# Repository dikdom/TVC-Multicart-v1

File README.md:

# TVC-Multicart-v1.1
A simple programmodule for the Videoton TVC computer that may contain multiple cartridge images

## English
This package contains the plans of a programmodule for the Videoton TV Compurer. The necessary
parts for building this cart could be obtained easily in 2018 and it costed around 2-3 USD. Cost
of the PCB depends on the manufacturer..

The cart may either contain a hex encoder switch or a 5 element DIP switch. These switches are there
for selecting the usable 16kB or area for the TVC during its startup.
The EEPROM IC has to be programmed, that each cartridge image starts at 16kB boundaries.
The populated EEPROM IC must be pin compatible with the AT29C0x0 (like AM29F0x0 or SST39SF0x0).
Using the HEX encoder one can select up to 16 images, so using an 512kB EEPROM this is not enough (16 images
are just the half of the complete eeprom). That is why there is a pin pad pair for the A18 address line. 
That pin pair must be shorted to access the upper 256kB area (ROM images from 17-32). This jumper is not required
when using the DIP switch, that contains a switch for the A18 line also.
The HEX encoder does the same as the DIP switch: it selects the proper lines on the EEPROM, just it is done by 
rotating the rotary switch.

These schematics were designed using the CADSoft Eagle 8.3.1, free software. The plans (schematics and board layout) 
can also be found, so you may change them at your own will.

You can find the edge connector's library and the cart itself in the eagle-lib directory. The 32k/64k and
the 64k+ machines have different line layout. There is no FAST line and the data lines are gated in the
64k+ machine.

Required parts:
- TVC Multicart v1.1 PCB
- DIP-32 IC socket
- eeprom (eg. SST39SF020)
- 100nF, (min) 16V, 2# ceramic capacitor
- 5+1 resistor network, 10k
- 5 DIP switch, OR
- 16 value hex-encoder

Use it wisely!

Sándor Vass, 2018-09-27

## Magyarul

Ez a csomag egy olyan nyáklap terveit tartalmazza, melyet alkatrésszekkel 
megfelelően ellátva a méltán híres Videoton TV Computerhez egy ún. multicart
cartridge készíthető. A carthoz szükséges alkatrészek 2018-ban kereskedelmi
forgalomban kaphatóak s kb 800Ft-ba kerülnek összesen. A nyáklap legyártásának
költsége gyártófüggő.

A nyáklapon egy forgatható hex enkóder és/vagy egy 5 elemű DIP kapcsolósor 
helyezhető el melyek segítségével lehet kiválasztani, hogy a TVC melyik 16kB -os 
tartományt (bankot) láthassa bekapcsoláskor/resetkor.
Az eeprom ICt úgy kell felprogramozni, hogy 16kB -onként 1-1 cartridge image
kezdődjön, így tudja az adott cartridge image-ét a TVC futtatni.
Az eepromnak lábkompatibilisnek kell lennie az AT29C040 -es ICvel (ilyenek pl.
az AM29F0x0 vagy a SST39SF0x0).
A hex enkóderrel legfeljebb 16 különböző bankot lehet kiválasztani, ez
egy 512kB -os eeprom esetében kevés lenne (pont fele a szükségesnek), ezért 
raktam a lapra egy érintkező párt az A18 lábnak. Ide egy 2x1 -es tüskesor rakható 
(egy jumperrel) vagy egy kapcsoló forrasztható: ezzel lehet kiválasztani, 
hogy az alsó, vagy a fölső 16 bank közül lehessen választani a tekerhető gombbal.
Zárva az érintkező párt az IC A18 -as lába 1-et kap, egyébként 0-át.
A hex-enkóder egy 6 kivezetéses, elforgatható kapcsoló, amely állásától
függően binárisan változtatja a kivezetéseit - 2 GND és 4 kapcsoló láb miatt
van csak 16 lehetséges állapota. Ez a forgatható kapcsoló kiválóan alkalmas az
eeprom A14-A17 lábainak állítására. Ha az eeprom mérete csak 256kB vagy
128kB, akkor nincs szükség a külső kapcsolóra, mert ilyenkor nincs A18 vonal.
A hex-enkóder mellett egy DIP kapcsolósor is beültethető a nyáklapba. Ebben az
esetben sincs szükség a külső kapcsolóra, mivel a DIP kapcsolósor tartalmazza
az A18-as vonal kapcsolóját is.

Ezeket a terveket a CADSoft Eagle 8.3.1, ingyenes verzióval terveztem, a kapcsolási 
rajz (.sch) és a nyákrajzolat (.brd) is mellékelve van, ha változtatásra van szükség.

Megtalálható az eagle-lib könyvtárban alkatrészként a cartrdige élcsatlakozója 
32k/64k és 64k+ gépekhez külön, illetve az egész cartridge, kontúrral, furatokkal
(ahol a gyári cartoknak is a furatuk található), ez szintén 32k/64k és 64k+ gépekhez.
A 64k+ gépeken nincs kivezetve a FAST jel, illetve itt az adatvonalak kapuzva vannak, 
nem közvetlenül a CPU-tól jön a jel.

Szükséges alkatrészek:
- TVC Multicart v1.1 nyáklap
- DIP-32 IC foglalat
- eeprom (pl. SST39SF020)
- 100nF, (min) 16V, 2raszteres kerámia kondenzátor
- 5+1 ellenálláshíd, 10k
- 5 elemű DIP kapcsolósor, vagy
- 16 értékű hex-enkóder

Használd egészséggel!

Vass Sándor, 2018-09-27

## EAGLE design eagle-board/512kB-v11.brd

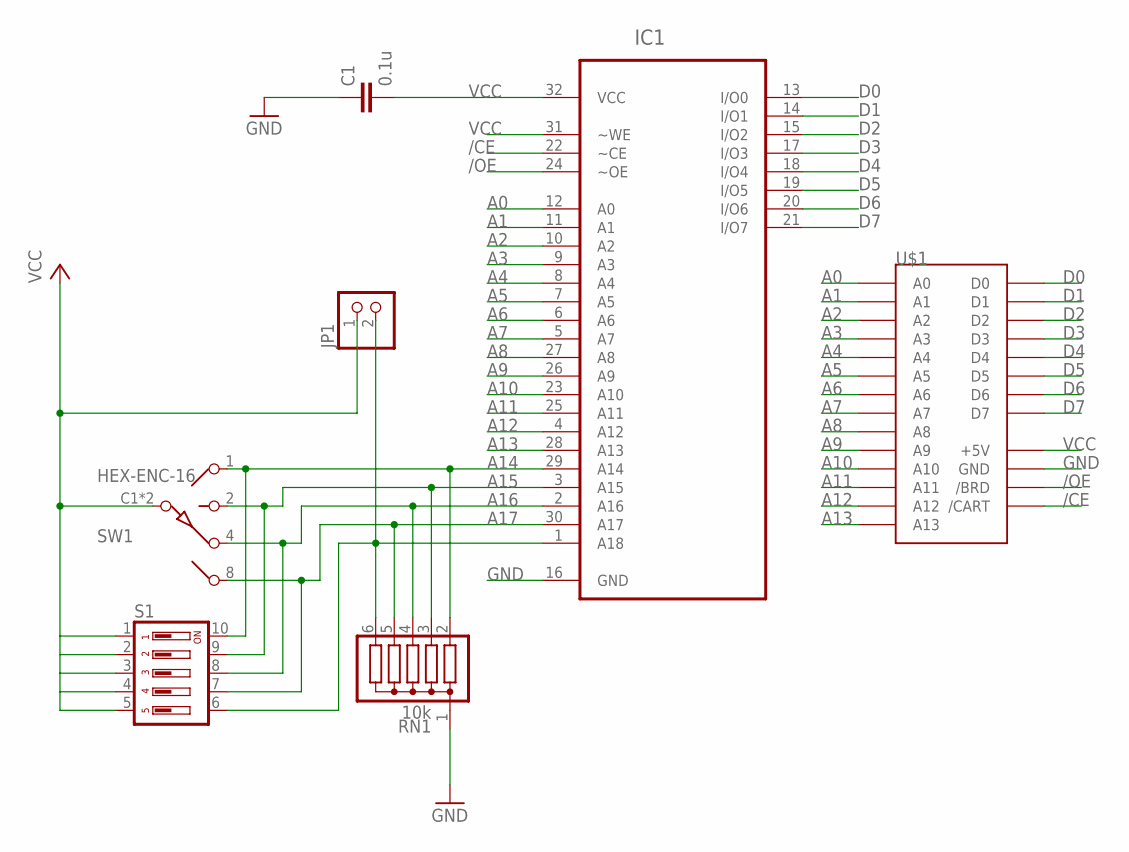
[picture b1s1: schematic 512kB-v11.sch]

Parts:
C1: 0.1u; C050-024X044
IC1: AT29C040; DIP254P1524X482-32
JP1: PINHD-1X2; 1X02
RN1: 10k; SIL6
S1: DIP05YL
SW1: HEX-ENC-16; SW-C16
U$1: TVC-CARD+; TVC-CART-CARD

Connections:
/CE: IC1.22 (~CE), U$1.BTM23 (/CART)
/OE: IC1.24 (~OE), U$1.BTM24 (/BRD)
A0: IC1.12 (A0), U$1.TOP25 (A0)
A1: IC1.11 (A1), U$1.TOP2 (A1)
A2: IC1.10 (A2), U$1.TOP24 (A2)
A3: IC1.9 (A3), U$1.TOP1 (A3)
A4: IC1.8 (A4), U$1.TOP21 (A4)
A5: IC1.7 (A5), U$1.TOP14 (A5)
A6: IC1.6 (A6), U$1.TOP18 (A6)
A7: IC1.5 (A7), U$1.TOP17 (A7)
A8: IC1.27 (A8), U$1.TOP15 (A8)
A9: IC1.26 (A9), U$1.TOP19 (A9)
A10: IC1.23 (A10), U$1.TOP22 (A10)
A11: IC1.25 (A11), U$1.TOP20 (A11)
A12: IC1.4 (A12), U$1.TOP16 (A12)
A13: IC1.28 (A13), U$1.TOP23 (A13)
A14: IC1.29 (A14), RN1.2, S1.10, SW1.1
A15: IC1.3 (A15), RN1.3, S1.9, SW1.2
A16: IC1.2 (A16), RN1.4, S1.8, SW1.4
A17: IC1.30 (A17), RN1.5, S1.7, SW1.8
D0: IC1.13 (I/O0), U$1.TOP4 (D0)
D1: IC1.14 (I/O1), U$1.TOP5 (D1)
D2: IC1.15 (I/O2), U$1.TOP6 (D2)
D3: IC1.17 (I/O3), U$1.TOP7 (D3)
D4: IC1.18 (I/O4), U$1.TOP8 (D4)
D5: IC1.19 (I/O5), U$1.TOP9 (D5)
D6: IC1.20 (I/O6), U$1.TOP10 (D6)
D7: IC1.21 (I/O7), U$1.TOP3 (D7)
GND: C1.1, IC1.16 (GND), RN1.1, U$1.BTM1 (GND), U$1.BTM2 (GND), U$1.BTM3 (GND), U$1.BTM4 (GND), U$1.BTM5 (GND), U$1.BTM6 (GND), U$1.BTM7 (GND), U$1.BTM8 (GND)
unnamed: IC1.1 (A18), JP1.2, RN1.6, S1.6
VCC: C1.2, IC1.31 (~WE), IC1.32 (VCC), JP1.1, S1.1, S1.2, S1.3, S1.4, S1.5, SW1.C1 (C), SW1.C2 (C), U$1.BTM10 (+5V), U$1.BTM11 (+5V), U$1.BTM12 (+5V), U$1.BTM13 (+5V), U$1.BTM14 (+5V), U$1.BTM15 (+5V), U$1.BTM16 (+5V), U$1.BTM17 (+5V)

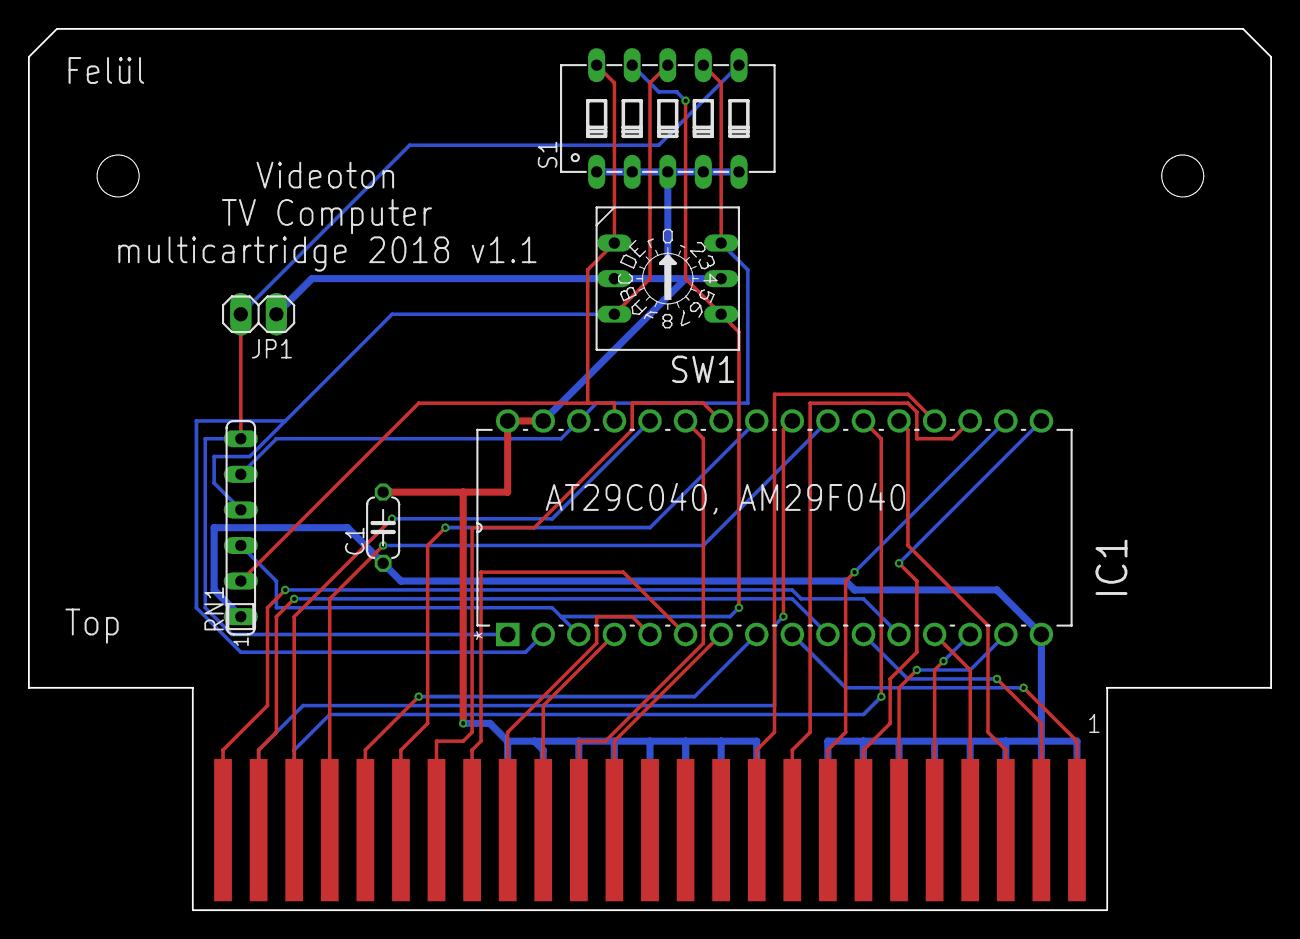
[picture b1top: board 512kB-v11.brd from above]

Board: 2 copper layers, 88.7 x 62.9 mm, 7 parts (0 on the bottom side), 31 nets.
